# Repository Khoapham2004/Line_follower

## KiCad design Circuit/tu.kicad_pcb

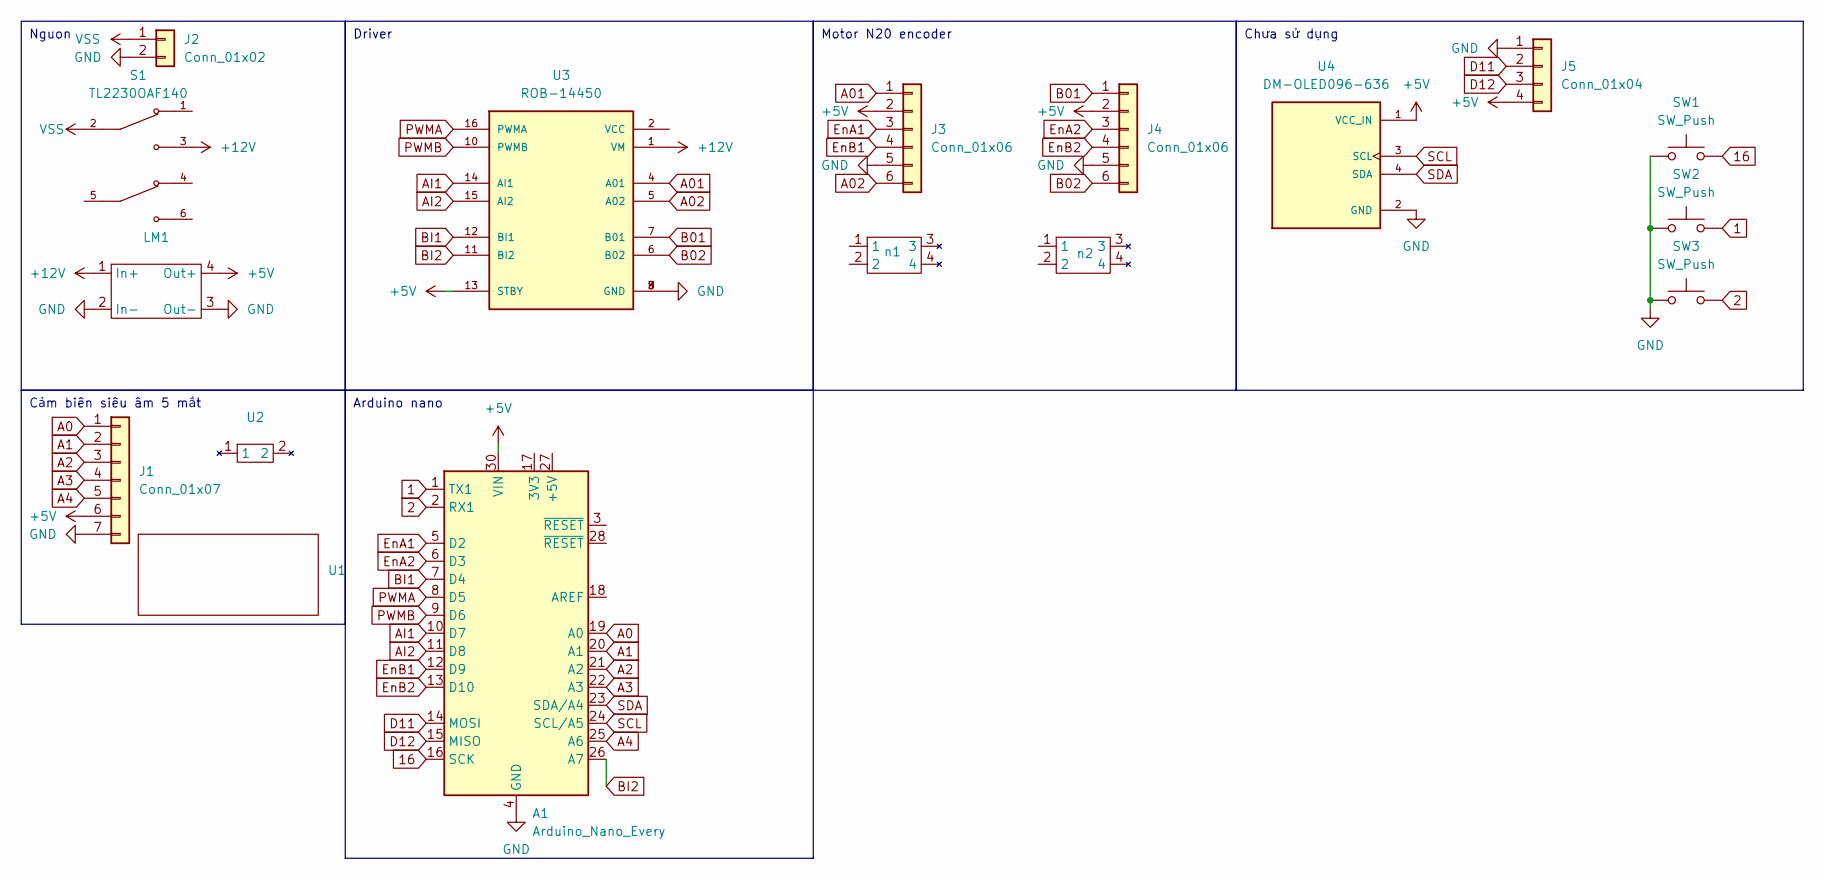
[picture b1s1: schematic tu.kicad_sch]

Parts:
A1: Arduino_Nano_Every; Arduino_Nano
J1: Conn_01x07; PinHeader_1x07_P2.54mm_Vertical
J2: Conn_01x02; PinHeader_1x02_P2.54mm_Vertical
J3, J4: Conn_01x06; PinHeader_1x06_P1.27mm_Vertical
J5: Conn_01x04; PinHeader_1x04_P2.54mm_Vertical
LM1: Lm2596
S1: TL2230OAF140; SW_6 pins 8.5×8.5MM; PARTREV E
SW1, SW2, SW3: SW_Push; SW_PUSH_6mm_H9.5mm
U1: Module_line
U2: mat_trau
U3: ROB-14450; MODULE_ROB-14450; PARTREV 11-13-17
U4: DM-OLED096-636; MODULE_DM-OLED096-636; PARTREV 2018-09-10
n1, n2: n20

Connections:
1: A1.1 (TX1), SW2.2
2: A1.2 (RX1), SW3.2
16: A1.16 (SCK), SW1.2
+5V: A1.30 (VIN), J1.6, J3.2, J4.2, J5.4, LM1.4 (Out+), U3.13 (STBY), U4.1 (VCC_IN)
+12V: LM1.1 (In+), S1.3, U3.1 (VM)
A0: A1.19 (A0), J1.1
A01: J3.1, U3.4 (A01)
A1: A1.20 (A1), J1.2
A02: J3.6, U3.5 (A02)
A2: A1.21 (A2), J1.3
A3: A1.22 (A3), J1.4
A4: A1.25 (A6), J1.5
AI1: A1.10 (D7), U3.14 (AI1)
AI2: A1.11 (D8), U3.15 (AI2)
B01: J4.1, U3.7 (B01)
B02: J4.6, U3.6 (B02)
BI1: A1.7 (D4), U3.12 (BI1)
BI2: A1.26 (A7), U3.11 (BI2)
D11: A1.14 (MOSI), J5.2
D12: A1.15 (MISO), J5.3
EnA1: A1.5 (D2), J3.3
EnA2: A1.6 (D3), J4.3
EnB1: A1.12 (D9), J3.4
EnB2: A1.13 (D10), J4.4
GND: A1.4 (GND), A1.29 (GND), J1.7, J2.2, J3.5, J4.5, J5.1, LM1.2 (In-), LM1.3 (Out-), SW1.1, SW2.1, SW3.1, U3.3 (GND), U3.8 (GND), U3.9 (GND), U4.2 (GND)
PWMA: A1.8 (D5), U3.16 (PWMA)
PWMB: A1.9 (D6), U3.10 (PWMB)
SCL: A1.24 (SCL/A5), U4.3 (SCL)
SDA: A1.23 (SDA/A4), U4.4 (SDA)
VSS: J2.1, S1.2

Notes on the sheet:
Chưa sử dụng
Driver
Cảm biên siêu âm 5 mắt
Nguon
Arduino nano
Motor N20 encoder

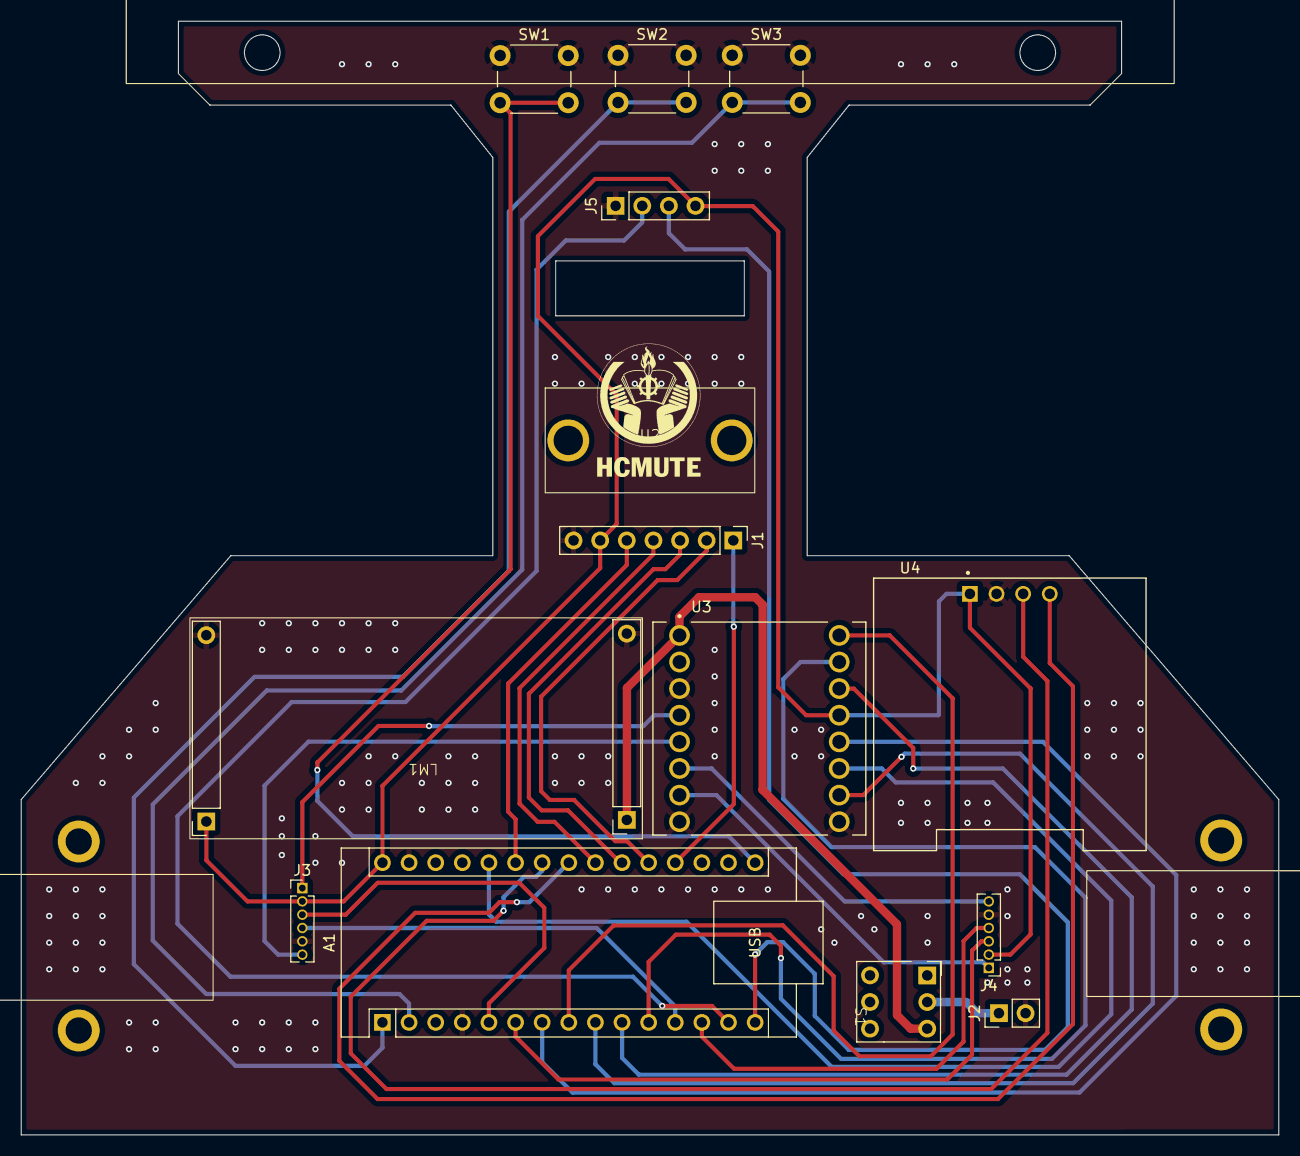
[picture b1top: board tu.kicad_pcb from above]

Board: 2 copper layers, 120.0 x 106.3 mm, 17 parts (0 on the bottom side), 30 nets.

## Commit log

2025-06-09 Create ,
